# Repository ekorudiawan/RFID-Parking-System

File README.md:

# RFID-Parking-System
RFID Parking System

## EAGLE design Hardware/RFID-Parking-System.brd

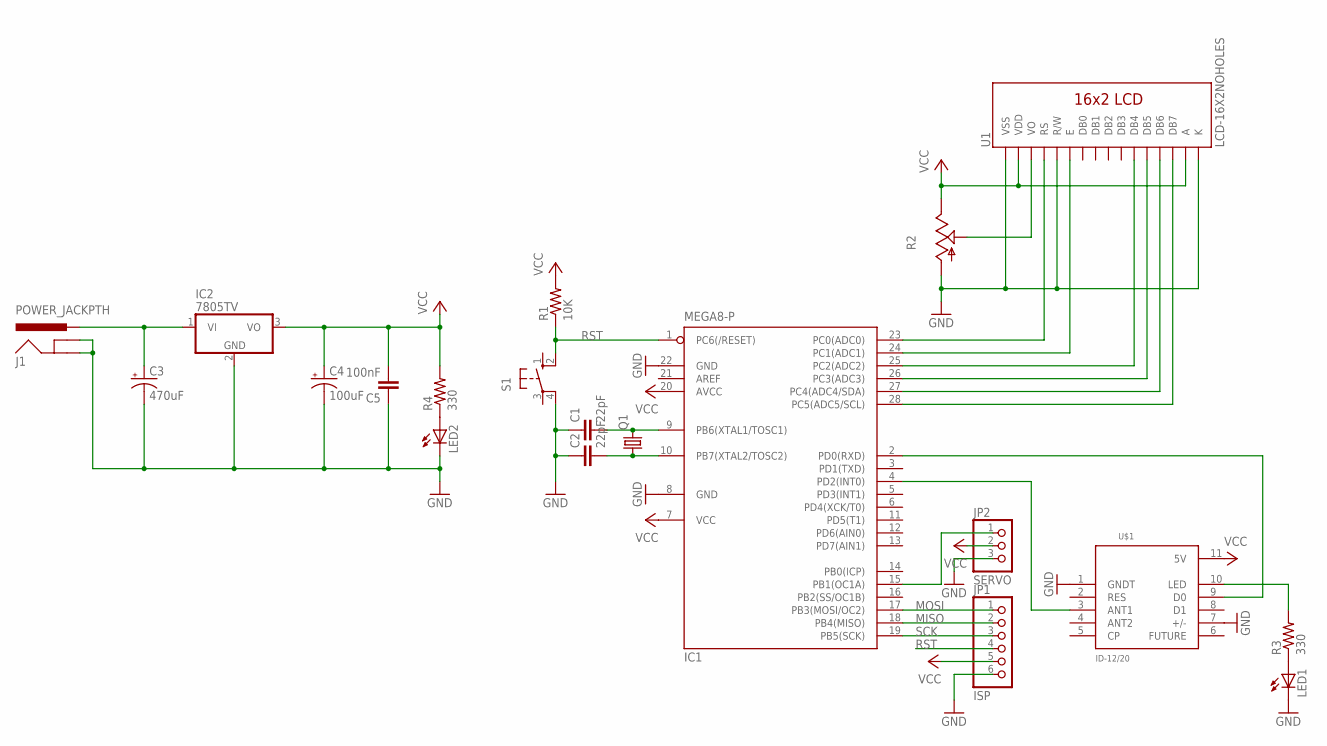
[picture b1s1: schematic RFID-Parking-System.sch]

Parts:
C1, C2: 22pF; C025-024X044
C3: 470uF; E2,5-6
C4: 100uF; E2,5-6
C5: 100nF; C025-024X044
IC1: MEGA8-P; DIL28-3
IC2: 7805TV; TO220V
J1: POWER_JACKPTH; POWER_JACK_PTH
JP1: ISP; 1X06
JP2: SERVO; 1X03
LED1, LED2: LED3MM
Q1: CRYSTALHC49S; HC49/S
R1: 10K; 0207/10
R2: TRIM_US-CA6V; CA6V
R3, R4: 330; 0207/10
S1: 10-XX; B3F-10XX
U1: LCD-16X2NOHOLES; LCD-16X2_NOHOLES
U$1: ID-12/20; ID-12

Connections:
GND: C1.1, C2.1, C3.-, C4.-, C5.1, IC1.8 (GND), IC1.22 (GND), IC2.2 (GND), J1.GND, J1.GNDBREAK, JP1.6, JP2.3, LED1.K (C), LED2.K (C), R2.A, S1.4 (P1), U1.1 (VSS), U1.5 (R/W), U1.16 (K), U$1.1 (GNDT), U$1.7 (+/-)
MISO: IC1.18 (PB4(MISO)), JP1.2
MOSI: IC1.17 (PB3(MOSI/OC2)), JP1.1
unnamed: C1.2, IC1.9 (PB6(XTAL1/TOSC1)), Q1.2
unnamed: C2.2, IC1.10 (PB7(XTAL2/TOSC2)), Q1.1
unnamed: IC1.15 (PB1(OC1A)), JP2.1
unnamed: R2.S, U1.3 (VO)
unnamed: IC1.23 (PC0(ADC0)), U1.4 (RS)
unnamed: IC1.24 (PC1(ADC1)), U1.6 (E)
unnamed: IC1.25 (PC2(ADC2)), U1.11 (DB4)
unnamed: IC1.26 (PC3(ADC3)), U1.12 (DB5)
unnamed: IC1.27 (PC4(ADC4/SDA)), U1.13 (DB6)
unnamed: IC1.28 (PC5(ADC5/SCL)), U1.14 (DB7)
unnamed: IC1.4 (PD2(INT0)), U$1.3 (ANT1)
unnamed: IC1.2 (PD0(RXD)), U$1.9 (D0)
unnamed: LED1.A, R3.1
unnamed: R3.2, U$1.10 (LED)
unnamed: C3.+, IC2.1 (VI), J1.PWR
unnamed: LED2.A, R4.1
RST: IC1.1 (PC6(/RESET)), JP1.4, R1.1, S1.2 (S1)
SCK: IC1.19 (PB5(SCK)), JP1.3
VCC: C4.+, C5.2, IC1.7 (VCC), IC1.20 (AVCC), IC2.3 (VO), JP1.5, JP2.2, R1.2, R2.E, R4.2, U1.2 (VDD), U1.15 (A), U$1.11 (5V)

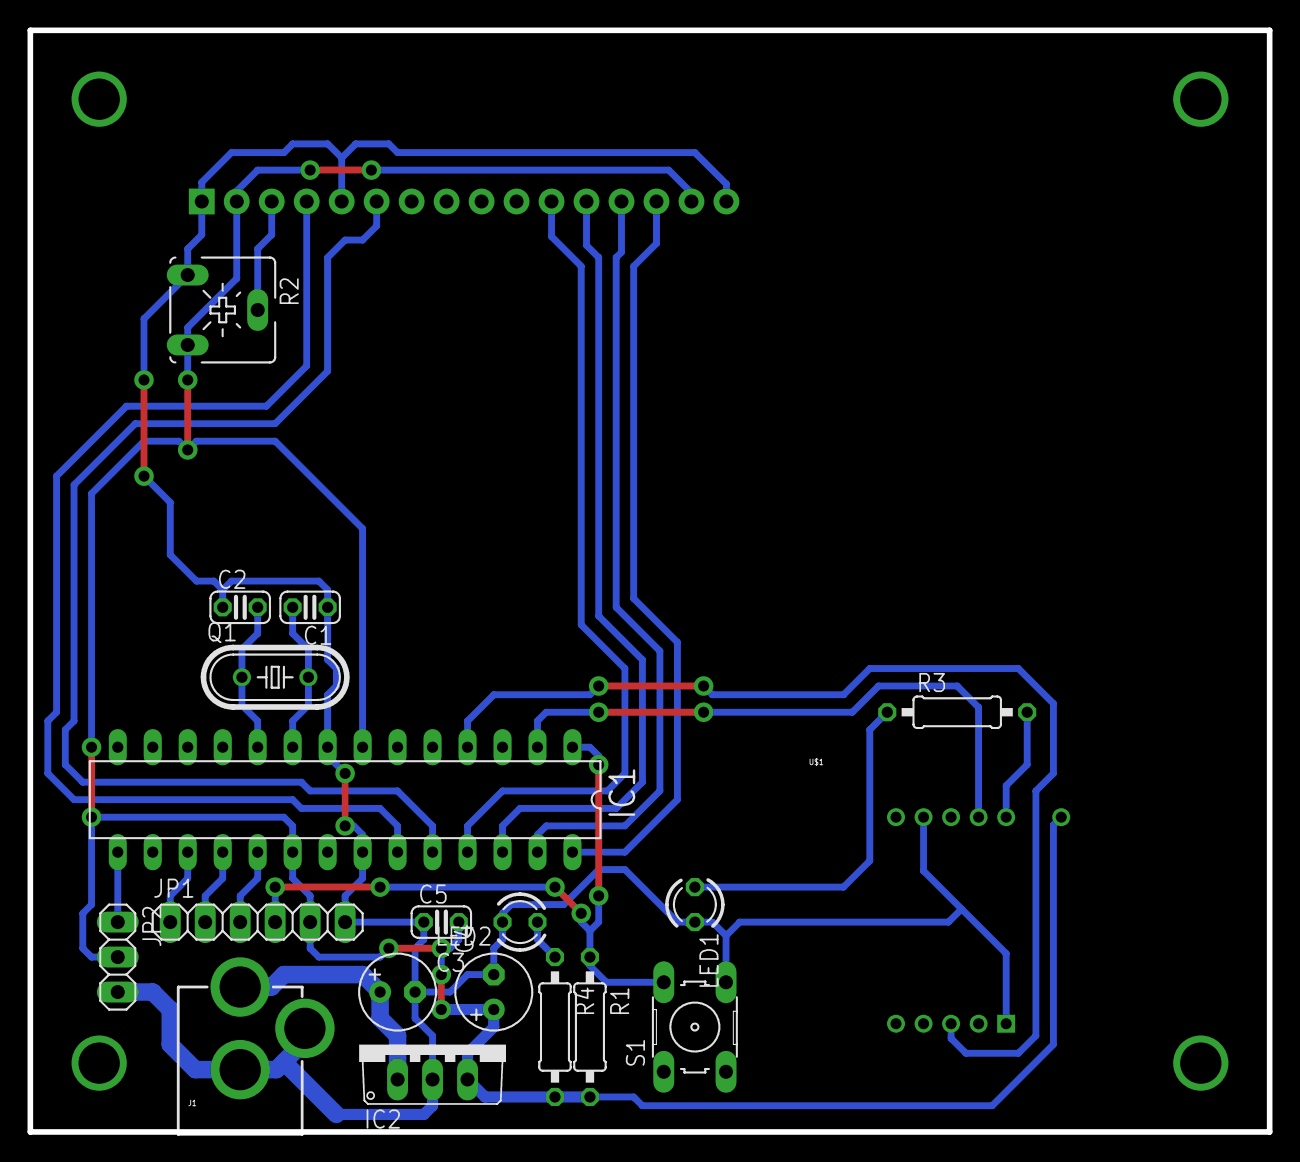
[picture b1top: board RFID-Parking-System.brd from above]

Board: 2 copper layers, 90.0 x 80.0 mm, 20 parts (0 on the bottom side), 22 nets.

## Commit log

2017-10-03 Added HW & SW Files

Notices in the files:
parts and their libraries:
SparkFun-RF: Licensing: CC v3.0 Share-Alike You are welcome to use this library for commercial purposes.
